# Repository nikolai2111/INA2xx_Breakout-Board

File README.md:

# INA2xx_Breakout-Board <!-- omit from toc -->
## Content <!-- omit from toc -->
- [1. Description](#1-description)
- [2. Folder structure](#2-folder-structure)
- [3. Usage](#3-usage)
- [4. License](#4-license)

## 1. Description
This is a very simple and low level breakout board for the INA2xx Current-Sense Amplifiers. Actually it's a breakout board for the 8-Pin and 10-Pin VSSOP footprint with only the footprint on it, nothing else.  The project was implemented with KiCAD, as single board or as a panel. It contains ready-to-use Gerber files for both, the single board and the panel (4x5 pcs.). For PCBWay Project click [here](https://www.pcbway.com/project/shareproject/INA2xx_Breakout_Board_Panel_9144f447.html).

## 2. Folder structure
TBC

## 3. Usage
Add instructions and examples here.

## 4. License
The hardware and its documentation is licensed under the CERN-OHL-P licence, which can be found [here](LICENSE).

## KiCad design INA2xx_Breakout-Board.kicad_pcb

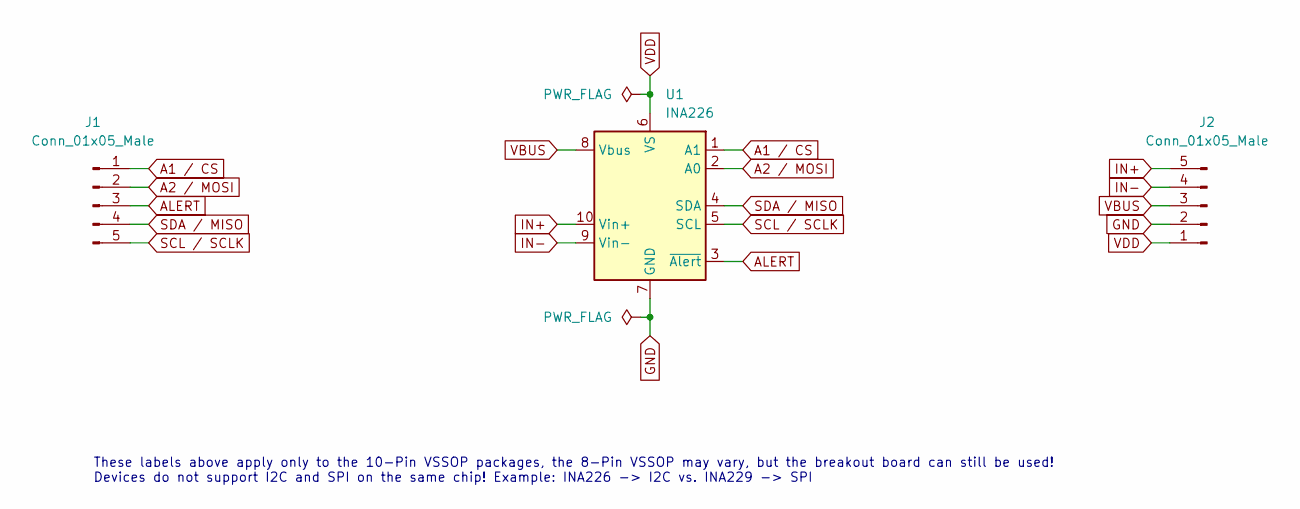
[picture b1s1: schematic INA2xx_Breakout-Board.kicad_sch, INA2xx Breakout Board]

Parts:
J1, J2: Conn_01x05_Male; PinHeader_1x05_P2.54mm_Vertical
U1: INA226; VSSOP-10_3x3mm_P0.5mm

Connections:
A1 / CS: J1.1, U1.1 (A1)
A2 / MOSI: J1.2, U1.2 (A0)
ALERT: J1.3, U1.3 (~Alert)
GND: J2.2, U1.7 (GND)
IN+: J2.5, U1.10 (Vin+)
IN-: J2.4, U1.9 (Vin-)
SCL / SCLK: J1.5, U1.5 (SCL)
SDA / MISO: J1.4, U1.4 (SDA)
VBUS: J2.3, U1.8 (Vbus)
VDD: J2.1, U1.6 (VS)

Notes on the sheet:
These labels above apply only to the 10-Pin VSSOP packages, the 8-Pin VSSOP may vary, but the breakout board can still be used! Devices do not support I2C and SPI on the same chip! Example: INA226 -> I2C vs. INA229 -> SPI

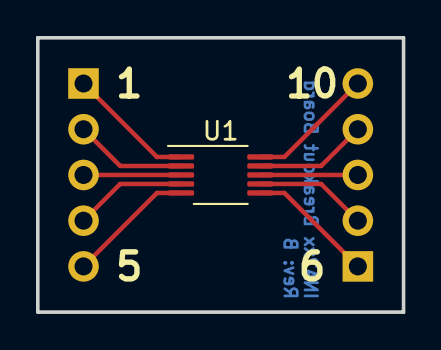
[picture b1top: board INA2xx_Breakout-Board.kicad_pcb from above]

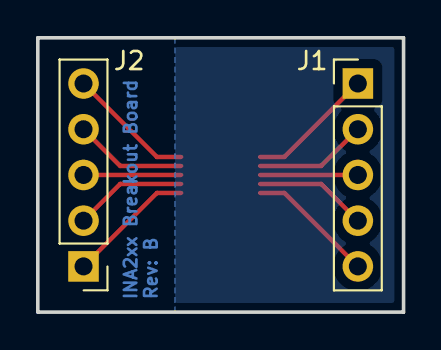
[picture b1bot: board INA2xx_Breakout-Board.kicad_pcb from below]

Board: 2 copper layers, 20.3 x 15.2 mm, 3 parts (2 on the bottom side), 10 nets.

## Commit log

2023-03-03 Mod: README file, added the default file structure Add: License and .gitignore
2023-03-03 Add: KiCAD project with schematic, pcb, panel (4x5 pcs.) and gerber files
2023-03-03 Mod: README, linked PCBWay project for easy order of the panel
2023-03-04 Del: Project file for panel, because not needed. Add: to .gitignore
2023-03-04 Mod: Bottom filled zone, added my logo to the solder mask and exported v-cuts
2023-03-06 Add: Project name and revision on the bottom solder mask, modified .gitignore
2023-03-06 Mod: Layout export, corrected issue date
2023-03-07 Mod: Updated the project name and revision to be on the copper layer now

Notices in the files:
INA2xx_Breakout-Board.kicad_sch:
License: CERN-OHL-P
